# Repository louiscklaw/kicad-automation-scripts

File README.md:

# KICAD automation script

### build

- master

- develop

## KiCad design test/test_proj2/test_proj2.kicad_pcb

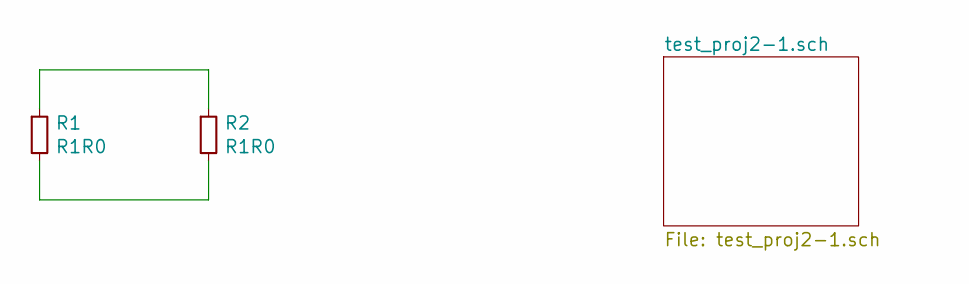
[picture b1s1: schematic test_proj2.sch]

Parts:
R1, R2: R1R0; R_4020_10251Metric

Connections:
unnamed: R1.1, R2.1
unnamed: R1.2, R2.2

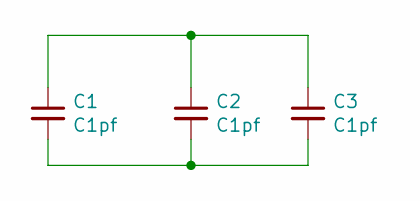
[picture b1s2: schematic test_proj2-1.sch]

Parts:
C1: C1pf; C_2816_7142Metric
C2: C1pf; C_2512_6332Metric_Pad1.52x3.35mm_HandSolder
C3: C1pf; C_2225_5664Metric_Pad1.80x6.60mm_HandSolder

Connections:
unnamed: C1.1, C2.1, C3.1
unnamed: C1.2, C2.2, C3.2

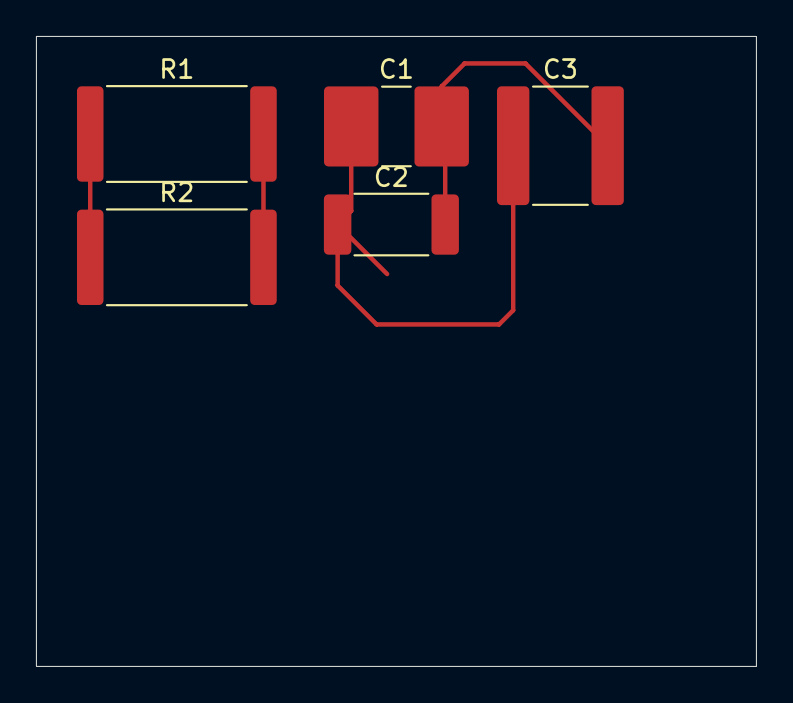
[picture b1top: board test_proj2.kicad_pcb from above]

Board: 2 copper layers, 40.0 x 35.0 mm, 5 parts (0 on the bottom side), 4 nets.

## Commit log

2019-12-27 init commit,
2019-12-28 add credentials,
2019-12-28 update and test,
2019-12-28 fix merge script,
2019-12-28 fix var name,
2019-12-28 fix build steps,
2019-12-28 split build_docker from build.sh,
2019-12-28 update build.sh to let the script basically working,
2019-12-28 add ls command to list output files,
2019-12-28 fix and try,
2019-12-28 update,
2019-12-28 try to fix permission denied by removing sudo,
2019-12-28 adding sudo to build.sh,
2019-12-28 add to build image before run rendering,
2019-12-28 init helloworld.html,
2019-12-28 add docker login to .travis.yml,
2019-12-28 add dbus-x11,
2019-12-28 init commit and test,
2019-12-28 init commit and test, (#1)
2019-12-28 init commit for relocate dockerfile,
2019-12-28 init commit and test, erc to python3,
2019-12-28 init commit, test and update for svg_gen to python3
2019-12-28 update to remove TODOs,
2019-12-29 update to delete ogv file from output directory,
2019-12-29 add test2,
2019-12-29 update and test, drc ok,
2019-12-29 update,.
2019-12-29 update to un-hardcode the sch file and pcb file,
2019-12-29 update README,
2019-12-30 init test,
2019-12-30 update test case,
2020-03-03 update docker credentials,
2020-03-03 update to split docker login and logout,
2020-03-03 ci: update add scrot in dockerfile,
2020-07-20 Bump psutil from 5.6.1 to 5.6.6 in /src
    Bumps [psutil](https://github.com/giampaolo/psutil) from 5.6.1 to 5.6.6.
    - [Release notes](https://github.com/giampaolo/psutil/releases)
    - [Changelog](https://github.com/giampaolo/psutil/blob/master/HISTORY.rst)
    - [Commits](https://github.com/giampaolo/psutil/compare/release-5.6.1...release-5.6.6)
2020-10-27 Bump cryptography from 2.8 to 3.2 in /_utils
    Bumps [cryptography](https://github.com/pyca/cryptography) from 2.8 to 3.2.
    - [Release notes](https://github.com/pyca/cryptography/releases)
    - [Changelog](https://github.com/pyca/cryptography/blob/master/CHANGELOG.rst)
    - [Commits](https://github.com/pyca/cryptography/compare/2.8...3.2)
